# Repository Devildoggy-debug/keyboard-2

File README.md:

# keyboard^2
This week I'm making a keyboard(the computer one) that works like a keyboard(The instrument).It has 16 keys, two buttons for Octave Up and down, A rechargeable battery and a speaker system.
## <ins>Reason for making it</ins>
I wanted to make a keyboard for this week, but when i looked up online I only saw tutorials on hot to make the tying kind of keyboard, and then I thought why not combine them both since they should functionally be the same if a speaker is added to the keyboard. This is also now doable on Kicad and allows me to have more resources to use while making said keyboard.
## <ins>How it works</ins>
The main chip used is a Raspberry Pro Pico 2, Its connected up to 16 keys set up in a matrix.The keys are in a 7x7 grid.There are an addiitonal 2 keys set up separately from the matrix to allow changing of octave. There is a speaker set up with an amplifier, speaker used is a Mini 8 ohm Speaker or a cavity speaker and the amplifier used is a Pam 8403.The battery used is a Lithium Ion Battery and is assisted by a TP4056 module.

<br>
## <ins>Features</ins>
- 16 Playable keys
- Rechargeable and portable
- Speakers that play 10Khz-37Khz
- The full catalogue of octaves
- If you know some coding, you can play any sound!!!!
## <ins>THE PCB</ins>

<br>

<br>
View PCB Here:

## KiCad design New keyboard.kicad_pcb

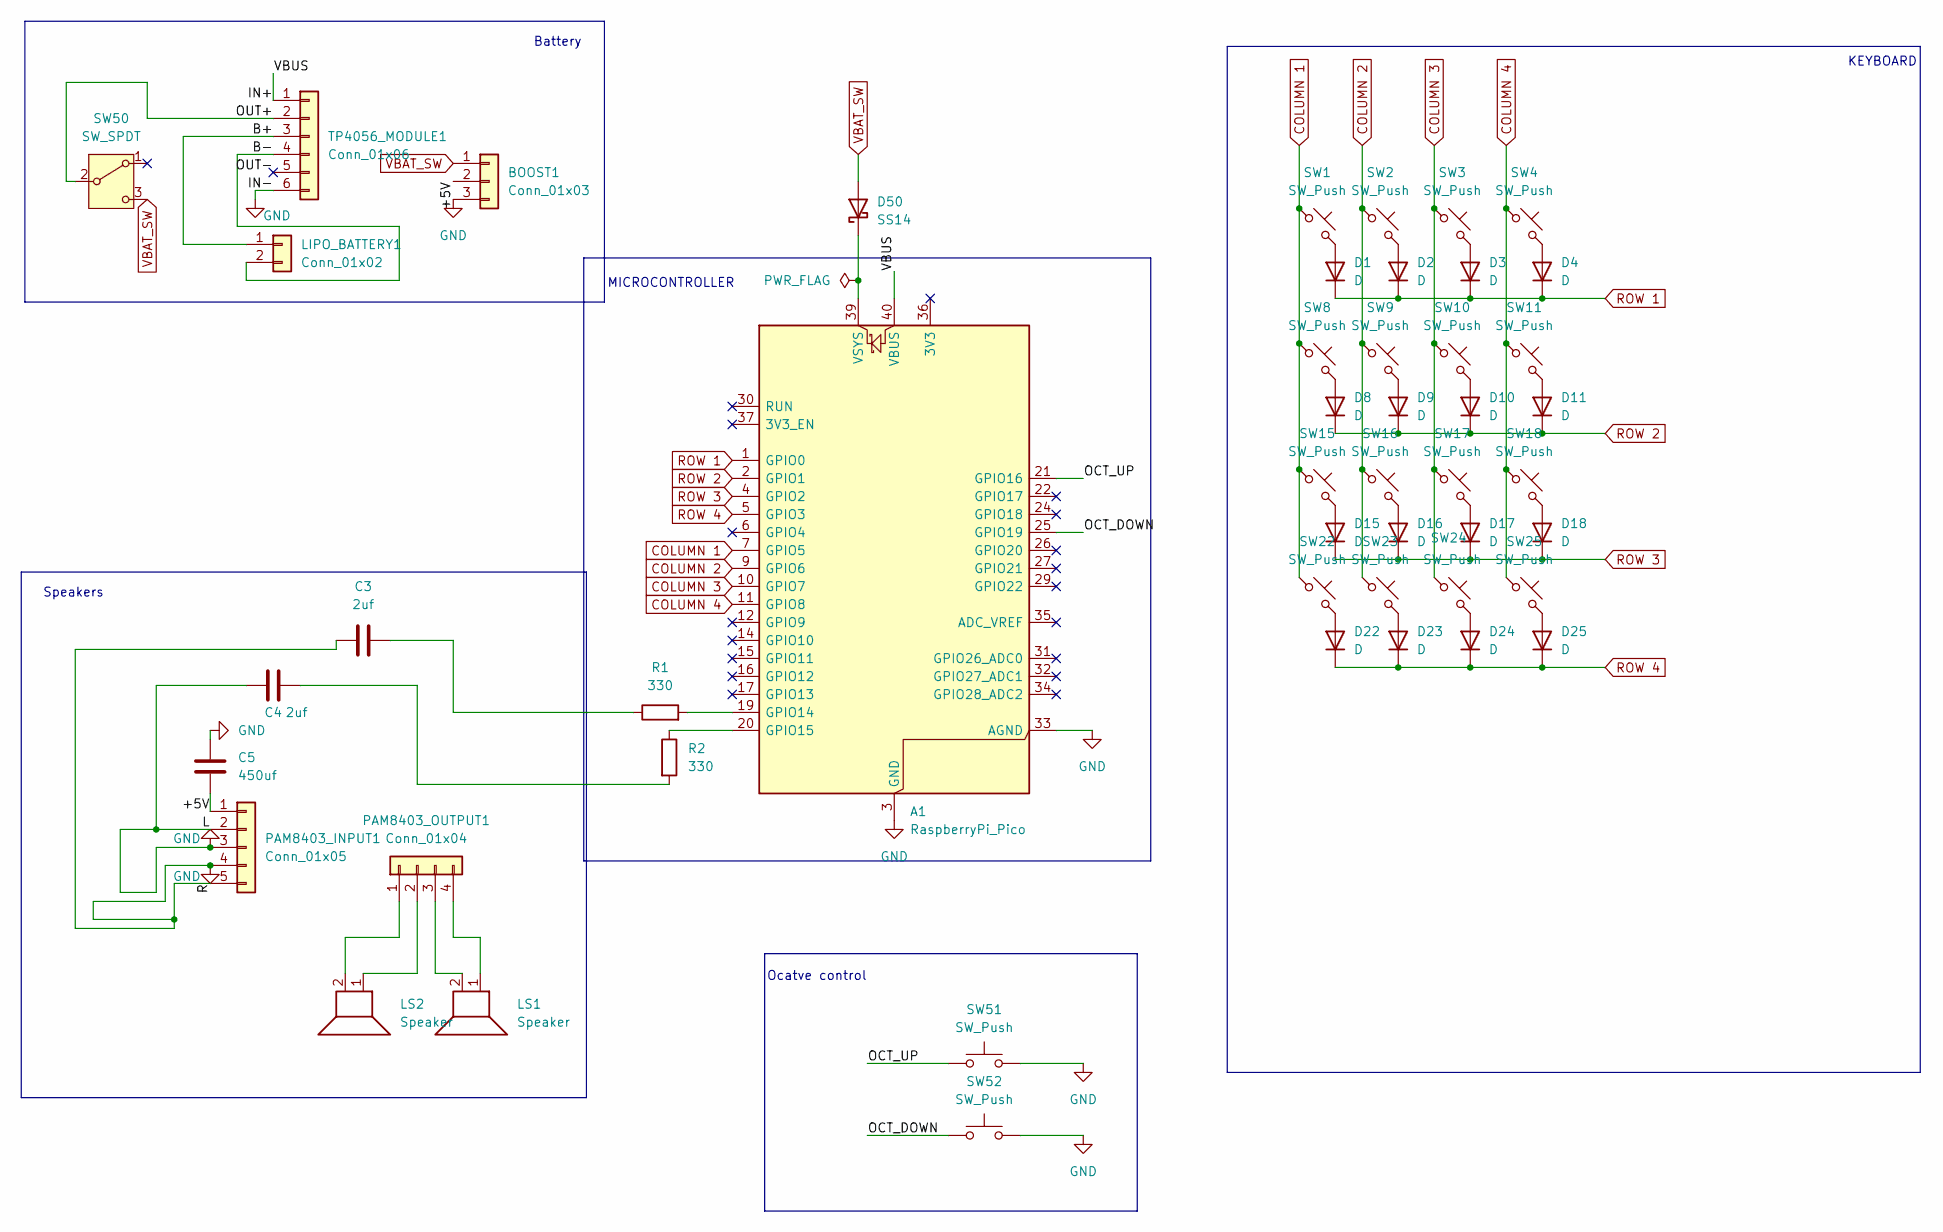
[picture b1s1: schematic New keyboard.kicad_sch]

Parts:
A1: RaspberryPi_Pico; RaspberryPi_Pico_Common_Unspecified
BOOST1: Conn_01x03; PinSocket_1x03_P2.54mm_Vertical
C3, C4: 2uf; C_Disc_D5.0mm_W2.5mm_P2.50mm
C5: 450uf; C_Disc_D5.0mm_W2.5mm_P2.50mm
D1, D2, D3, D4, D8, D9, D10, D11, D15, D16, D17, D18, D22, D23, D24, D25: D; Diode_DO-35
D50: SS14; D_DO-41_SOD81_P7.62mm_Horizontal
LIPO_BATTERY1: Conn_01x02; JST_PH_S2B-PH-K_1x02_P2.00mm_Horizontal
LS1, LS2: Speaker; TerminalBlock_TE_282834-2_1x02_P2.54mm_Horizontal
PAM8403_INPUT1: Conn_01x05; PinSocket_1x05_P2.54mm_Vertical
PAM8403_OUTPUT1: Conn_01x04; PinSocket_1x04_P2.54mm_Vertical
PWR_FLAG01: GND
R1, R2: 330; R_Axial_DIN0207_L6.3mm_D2.5mm_P2.54mm_Vertical
SW1, SW2, SW3, SW4, SW8, SW9, SW10, SW11, SW15, SW16, SW17, SW18, SW22, SW23, SW24, SW25, SW51, SW52: SW_Push; MX_PCB_1.00u
SW50: SW_SPDT; SW_Slide-03_Wuerth-WS-SLTV_10x2.5x6.4_P2.54mm
TP4056_MODULE1: Conn_01x06; PinSocket_1x06_P2.54mm_Vertical

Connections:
/+5V: BOOST1.2, C5.2, PAM8403_INPUT1.1
/B+: LIPO_BATTERY1.1, TP4056_MODULE1.3
/B-: LIPO_BATTERY1.2, TP4056_MODULE1.4
/IN+: A1.40 (VBUS), TP4056_MODULE1.1
/OCT_DOWN: A1.25 (GPIO19), SW52.1
/OCT_UP: A1.21 (GPIO16), SW51.1
/OUT+: SW50.2 (B), TP4056_MODULE1.2
/OUT-: TP4056_MODULE1.5
COLUMN 1: A1.7 (GPIO5), SW1.1, SW8.1, SW15.1, SW22.1
COLUMN 2: A1.9 (GPIO6), SW2.1, SW9.1, SW16.1, SW23.1
COLUMN 3: A1.10 (GPIO7), SW3.1, SW10.1, SW17.1, SW24.1
COLUMN 4: A1.11 (GPIO8), SW4.1, SW11.1, SW18.1, SW25.1
unnamed: A1.19 (GPIO14), R1.2
unnamed: A1.20 (GPIO15), R2.1
unnamed: A1.39 (VSYS), D50.1 (K)
unnamed: C3.2, R1.1
unnamed: C4.2, R2.2
unnamed: D1.2 (A), SW1.2
unnamed: D2.2 (A), SW2.2
unnamed: D3.2 (A), SW3.2
unnamed: D4.2 (A), SW4.2
unnamed: D8.2 (A), SW8.2
unnamed: D9.2 (A), SW9.2
unnamed: D10.2 (A), SW10.2
unnamed: D11.2 (A), SW11.2
unnamed: D15.2 (A), SW15.2
unnamed: D16.2 (A), SW16.2
unnamed: D17.2 (A), SW17.2
unnamed: D18.2 (A), SW18.2
unnamed: D22.2 (A), SW22.2
unnamed: D23.2 (A), SW23.2
unnamed: D24.2 (A), SW24.2
unnamed: D25.2 (A), SW25.2
unnamed: LS2.2, PAM8403_OUTPUT1.1
unnamed: LS2.1, PAM8403_OUTPUT1.2
unnamed: LS1.2, PAM8403_OUTPUT1.3
unnamed: LS1.1, PAM8403_OUTPUT1.4
ROW 1: A1.1 (GPIO0), D1.1 (K), D2.1 (K), D3.1 (K), D4.1 (K)
ROW 2: A1.2 (GPIO1), D8.1 (K), D9.1 (K), D10.1 (K), D11.1 (K)
ROW 3: A1.4 (GPIO2), D15.1 (K), D16.1 (K), D17.1 (K), D18.1 (K)
ROW 4: A1.5 (GPIO3), D22.1 (K), D23.1 (K), D24.1 (K), D25.1 (K)
VBAT_SW: BOOST1.1, D50.2 (A), SW50.3 (C)

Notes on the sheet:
KEYBOARD
Ocatve control
Battery
Speakers
MICROCONTROLLER

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
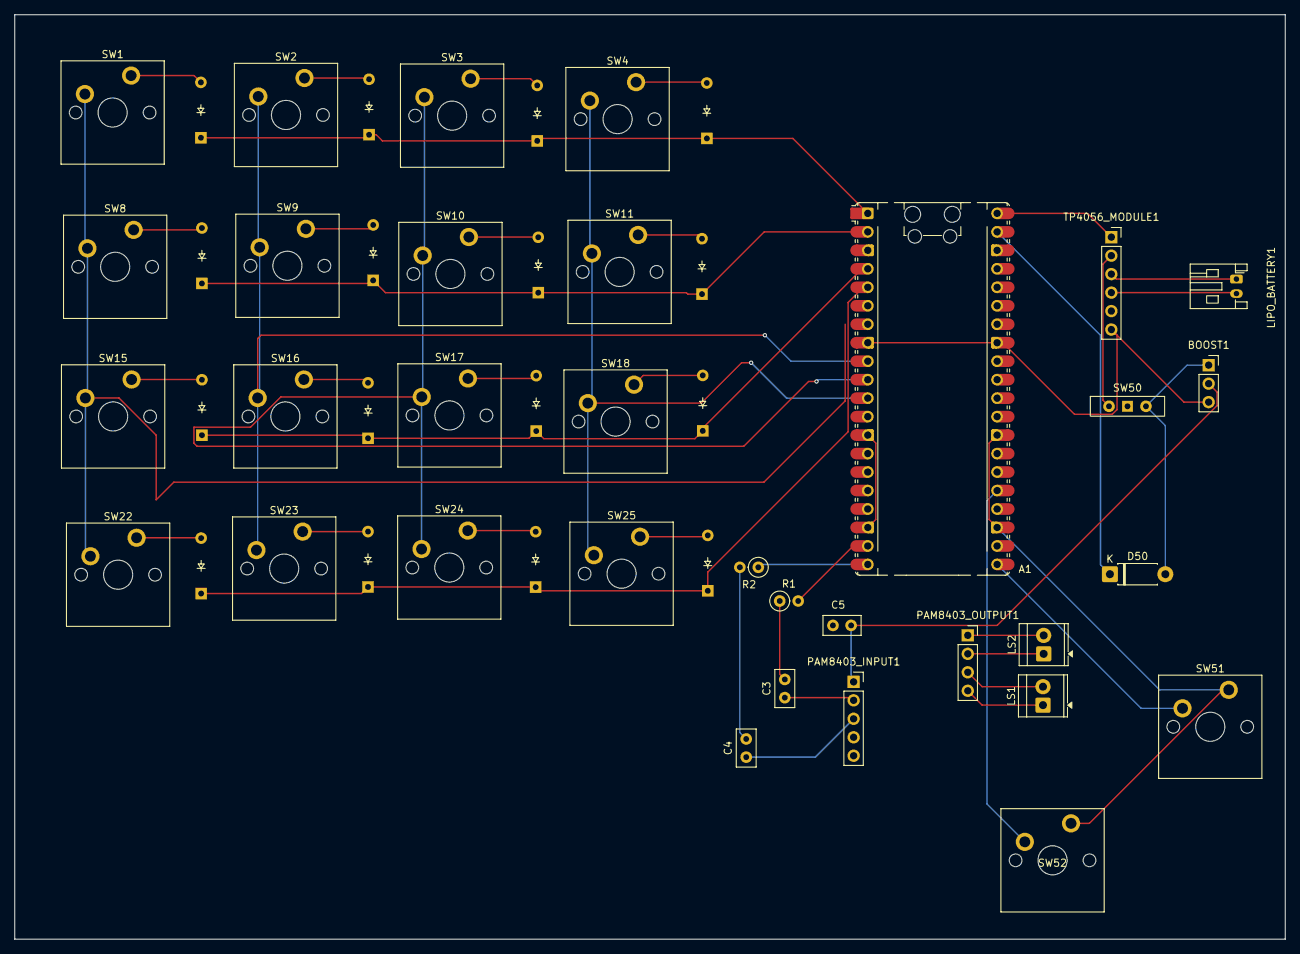
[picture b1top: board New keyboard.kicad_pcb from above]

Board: 2 copper layers, 174.7 x 127.1 mm, 49 parts (0 on the bottom side), 42 nets.
